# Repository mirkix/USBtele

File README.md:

# USBtele

USB FrSky SmartPort adapter

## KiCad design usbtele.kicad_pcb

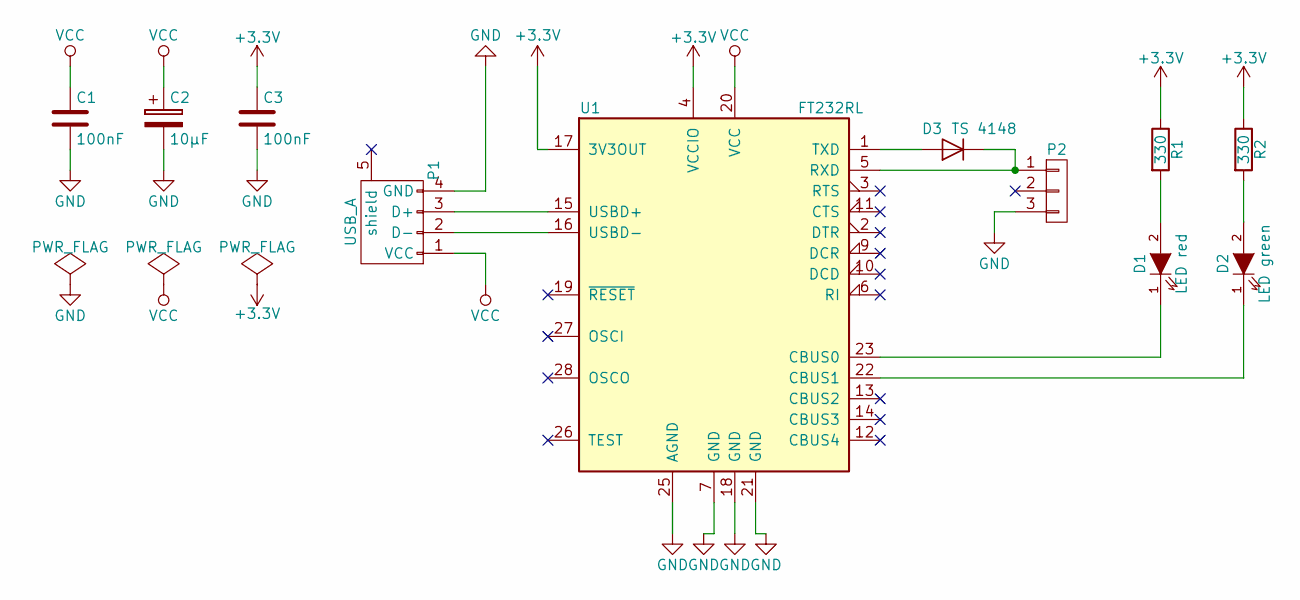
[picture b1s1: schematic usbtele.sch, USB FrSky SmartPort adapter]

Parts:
C1, C3: 100nF; C_1206
C2: 10µF; Tantalum_Case-C_EIA-6032-28_Hand
D1: LED red; LED_1206
D2: LED green; LED_1206
D3: TS 4148; SMD-1206_Pol
P1: USB_A; LUM2410-08
P2: CONN_01X03; Pin_Header_Straight_1x03
R1, R2: 330; R_1206
U1: FT232RL; SSOP-28_5.3x10.2mm_Pitch0.65mm

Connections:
+3V3: C3.1, R1.1, R2.1, U1.4 (VCCIO), U1.17 (3V3OUT)
GND: C1.2, C2.2, C3.2, P1.4 (GND), P2.3, U1.7 (GND), U1.18 (GND), U1.21 (GND), U1.25 (AGND)
unnamed: D1.1 (K), U1.23 (CBUS0)
unnamed: D1.2 (A), R1.2
unnamed: D2.1 (K), U1.22 (CBUS1)
unnamed: D2.2 (A), R2.2
unnamed: D3.1 (K), P2.1, U1.5 (RXD)
unnamed: D3.2 (A), U1.1 (TXD)
unnamed: P1.2 (D-), U1.16 (USBD-)
unnamed: P1.3 (D+), U1.15 (USBD+)
VCC: C1.1, C2.1, P1.1 (VCC), U1.20 (VCC)

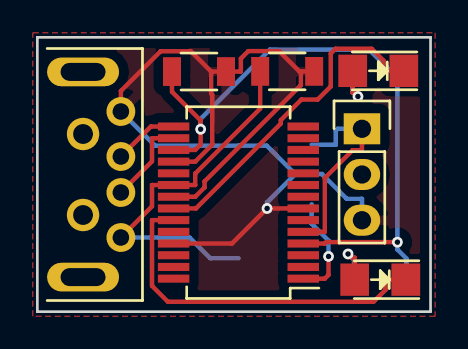
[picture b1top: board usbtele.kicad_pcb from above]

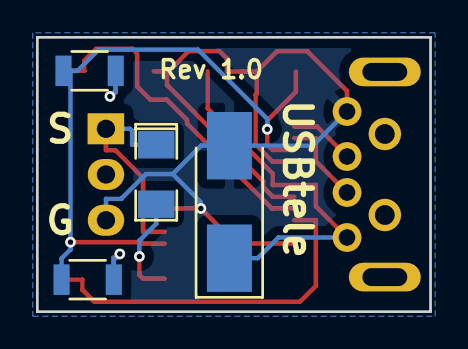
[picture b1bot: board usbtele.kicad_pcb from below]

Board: 2 copper layers, 21.8 x 15.2 mm, 11 parts (4 on the bottom side), 11 nets.

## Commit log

2016-12-28 Add Rev 1.0
2018-04-28 Add PDF schematic
